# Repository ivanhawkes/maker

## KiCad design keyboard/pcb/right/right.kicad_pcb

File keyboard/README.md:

# Personal Split Keyboard

A personal keyboard project based on an accepted left-hand switch-position prototype. The goal is two mirrored, rechargeable keyboard halves communicating over Bluetooth Low Energy (BLE) with a separate desk controller connected to the PC by USB. The owner intends to print the cases on a Bambu Labs X2D.

**Status (2026-11-24):** design in progress. Both PCB halves are generated and fully routed by script, and pass KiCad's design rule check; their fabrication files are generated and checked on the computer ([PCB design](docs/pcb.md#fabrication-outputs-2026-11-24)); the firmware for both halves and the dongle compiles ([firmware](firmware/README.md)). Each half has a schematic drawn from its board, with KiCad's electrical rules check clean. Nothing has been fabricated or flashed, and there is no final case yet. Nothing here is verified on hardware.

## Prototype

The original files are preserved together in [prototype/left-hand/](prototype/left-hand/):

- [test-pad.fcstd](prototype/left-hand/test-pad.fcstd): existing FreeCAD prototype and starting point for the left-hand design.
- [test-pad.step](prototype/left-hand/test-pad.step) and [test-pad.3mf](prototype/left-hand/test-pad.3mf): existing 3D files.
- [test-pad-baseplate.dxf](prototype/left-hand/test-pad-baseplate.dxf): existing baseplate drawing; the DXF declares millimetres.

The geometry, switch count, dimensions, and relationships between the source and exports still need to be verified in FreeCAD. The layout is accepted, but small changes may be needed later.

## Documentation

- [Concept](docs/concept.md): the agreed shape of the keyboard, covering layout, electronics, firmware, mechanics and scope.
- [Requirements](docs/requirements.md): agreed goals and acceptance criteria.
- [Architecture](docs/architecture.md): proposed mechanical, electrical, and firmware approach and research links.
- [Decisions](docs/decisions.md): open questions and their design implications.
- [Development plan](docs/development-plan.md): staged work and deliverables for the future agent.
- [PCB design](docs/pcb.md): decisions, electrical design, fab rules, parts list and results.
- [PCB routing](docs/pcb-routing.md): how the boards are routed by script, and what was learned.
- [Case design](docs/case.md): the printed case for keyboard 1, how it is generated and checked, and its limits.
- [Retro case](docs/case-retro.md): the 1970s case for keyboard 2, built round the first case's insides.
- [Dongle case](docs/dongle-case.md): the printed case for the hand-wired dongle, and its wiring.
- [Showcase scenes](docs/scenes.md): the Blender files and stills of both keyboards, and how they are made.
- [Target controller](docs/controller.md): the board bought, a nice!nano clone, and the tests it must pass.
- [Filament on hand](docs/filament-on-hand.md): the owner's spools, for choosing colours.
- [Parts](parts/README.md): local footprints, 3D models and datasheets for every part.
- [Verification plan](docs/verification.md): digital checks and physical tests to plan and record.
- [AGENTS.md](AGENTS.md): shared instructions for agents; [CLAUDE.md](CLAUDE.md) imports them for Claude Code.

## Generating Everything

Run these from `keyboard/` inside the devenv shell, in this order. Each step reads what the one
before it wrote, so after a change run that step and everything below it. Every generator
checks its own output and exits with 1 if a check fails. FreeCAD comes from the system, not
the devenv ([PCB design](docs/pcb.md#running-the-tools)).

**1. Layout** ([layout/README.md](layout/README.md))

```sh
python tools/layout.py build       # layout/generated/ from layout/layout.yaml
python tools/layout.py check       # 28 keys a half, no overlaps (cutouts, real keycap outlines), exact mirror, outputs fresh
```

**2. Boards and schematics** ([PCB design](docs/pcb.md)). These need KiCad's own Python:

```sh
K=$(nix-store -qR "$(dirname "$(dirname "$(readlink -f "$(which kicad-cli)")")")")
PY=$(echo "$K" | grep 'python3-3.14.*-env

Open this directory as the project and select the desired available model in your Claude-enabled client. In Claude Code, the root `CLAUDE.md` imports the shared instructions. Ask the agent to start with the prototype inspection and decision review in the development plan. The PCB commands are `python tools/pcb_generate.py` (boards and schematics) and `python tools/pcb_check.py` (see [PCB design](docs/pcb.md#running-the-tools)). Claude's instruction-file loading can be checked with `/context all` where supported.)/bin/python3
YAML=$(dirname "$(dirname "$(python3 -c 'import yaml; print(yaml.__file__)')")")
export PYTHONPATH=$(echo "$K" | grep 'kicad-base-10')/lib/python3.14/site-packages:$YAML

"$PY" tools/pcb_generate.py        # both boards, routed, and their schematics; about 15 s
"$PY" tools/pcb_check.py           # design rules, electrical rules, schematic parity; about 40 s
"$PY" tools/pcb_review.py          # the boards' nets against the firmware's matrix
"$PY" tools/fab_generate.py        # Gerbers, drill files, placement and parts list in pcb/fab/, checked; about 8 s

for s in left right; do            # 1:1 prints for checking parts against the board
  kicad-cli pcb export pdf --mode-single --black-and-white --ev \
    --layers F.Cu,F.SilkS,F.Fab,Edge.Cuts -o pcb/print/$s-front.pdf pcb/$s/$s.kicad_pcb
  kicad-cli pcb export pdf --mode-single --black-and-white --ev --mirror \
    --layers B.Cu,B.SilkS,B.Fab,Edge.Cuts -o pcb/print/$s-back.pdf pcb/$s/$s.kicad_pcb
done
```

**3. Firmware shield** ([firmware/README.md](firmware/README.md), which also has the build commands)

```sh
python tools/zmk_generate.py            # the ZMK shield from pcb/pins.yaml and the layout
python tools/zmk_generate.py --check    # the shield is up to date
```

**4. Cases** ([case](docs/case.md), [retro case](docs/case-retro.md), [dongle case](docs/dongle-case.md))

```sh
"$PY" tools/case_board.py                 # board outlines and part positions, for the cases
FreeCADCmd tools/case_generate.py         # keyboard 1: tray, plate, lid; about 3 minutes
FreeCADCmd tools/wedge_generate.py        # its tenting wedges; about 1 minute
FreeCADCmd tools/case_retro_generate.py   # keyboard 2, the retro case; about 4 minutes
FreeCADCmd tools/dongle_generate.py       # the dongle's case; a few seconds
```

**5. Showcase scenes** ([scenes](docs/scenes.md))

```sh
FreeCADCmd tools/scene_export.py                                 # meshes for Blender; about 1 minute
blender -b --python tools/scene_build.py                         # the two .blend files only
blender -b --python tools/scene_build.py -- --render             # and 20 stills at 1920 x 1080
blender -b --python tools/scene_build.py -- --render --size 2k   # 20 stills at 2560 x 1440
blender -b --python tools/scene_build.py -- --render --size 4k   # 20 stills at 3840 x 2160
```

Stills go to `cad/scenes/renders/1080p/`, `2k/` or `4k/`. Add `--only kb1` or `--only retro` for
one keyboard. Rendering is on both graphics cards: the 4k set took under 10 minutes here.
Without a usable graphics card it falls back to the CPU, about eight times slower.

## Starting With Claude

Open this directory as the project and select the desired available model in your Claude-enabled client. In Claude Code, the root `CLAUDE.md` imports the shared instructions. Ask the agent to start with the prototype inspection and decision review in the development plan. The PCB commands are `python tools/pcb_generate.py` (boards and schematics) and `python tools/pcb_check.py` (see [PCB design](docs/pcb.md#running-the-tools)). Claude's instruction-file loading can be checked with `/context all` where supported.

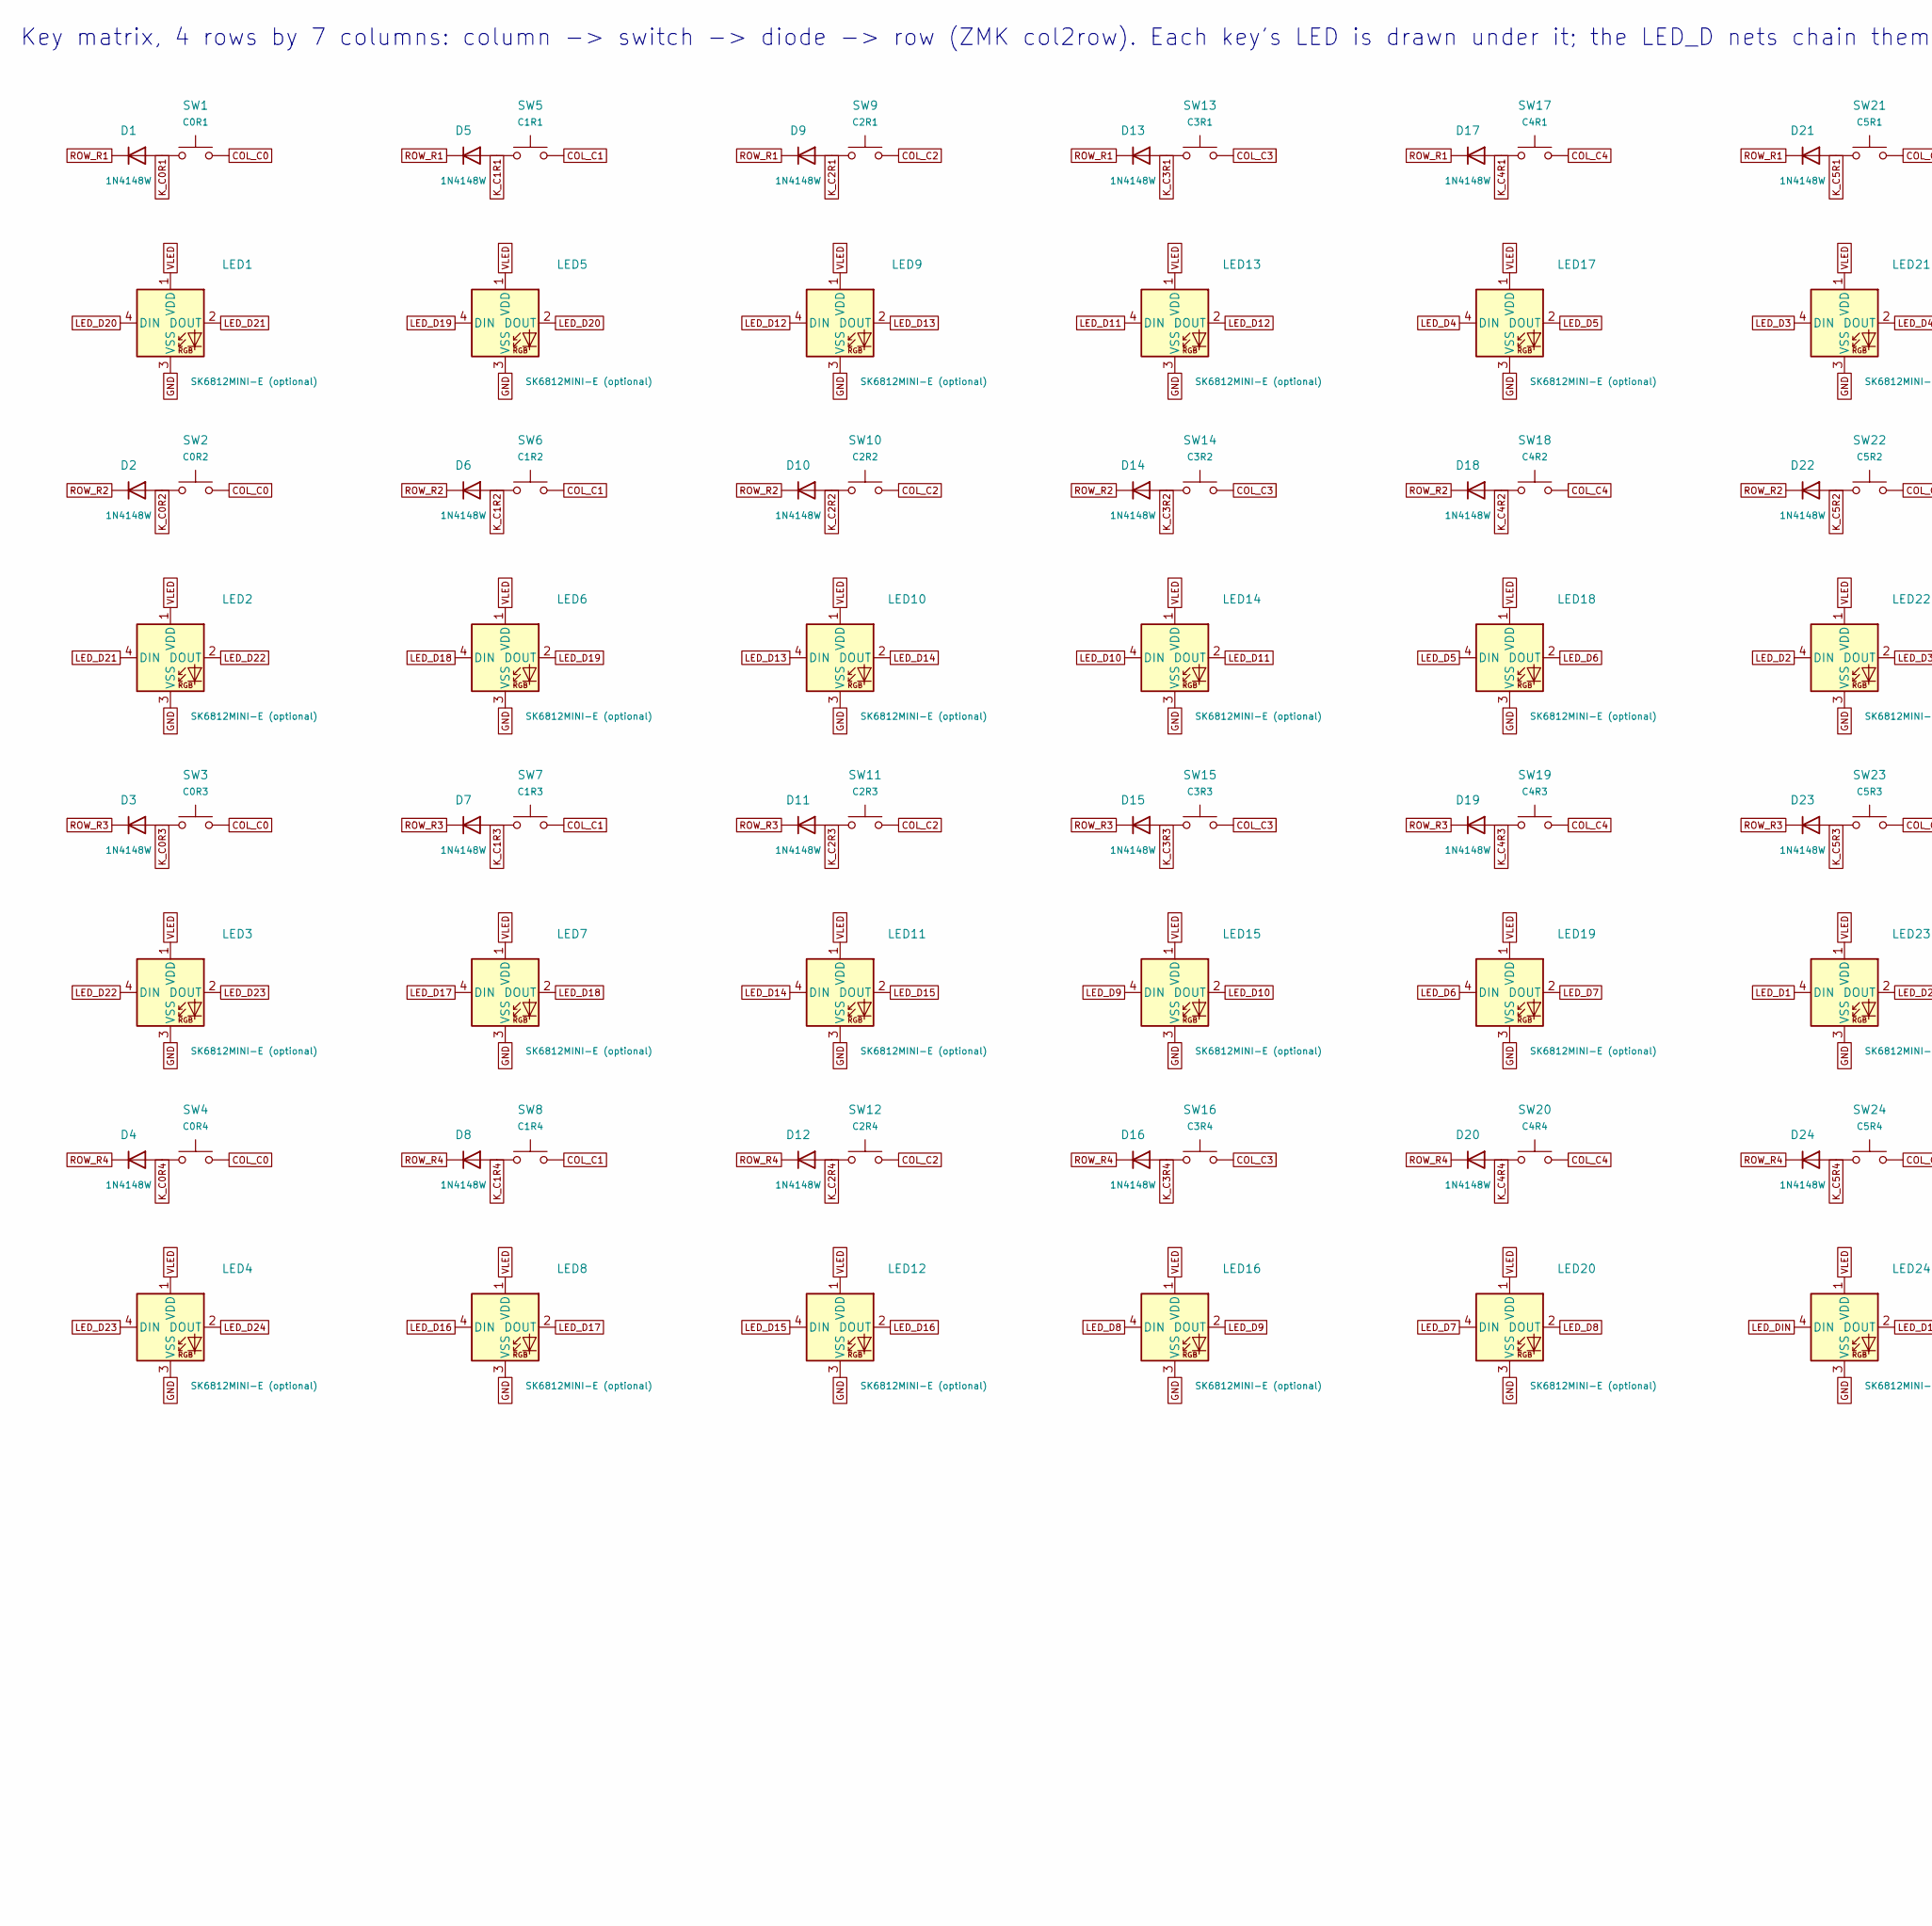
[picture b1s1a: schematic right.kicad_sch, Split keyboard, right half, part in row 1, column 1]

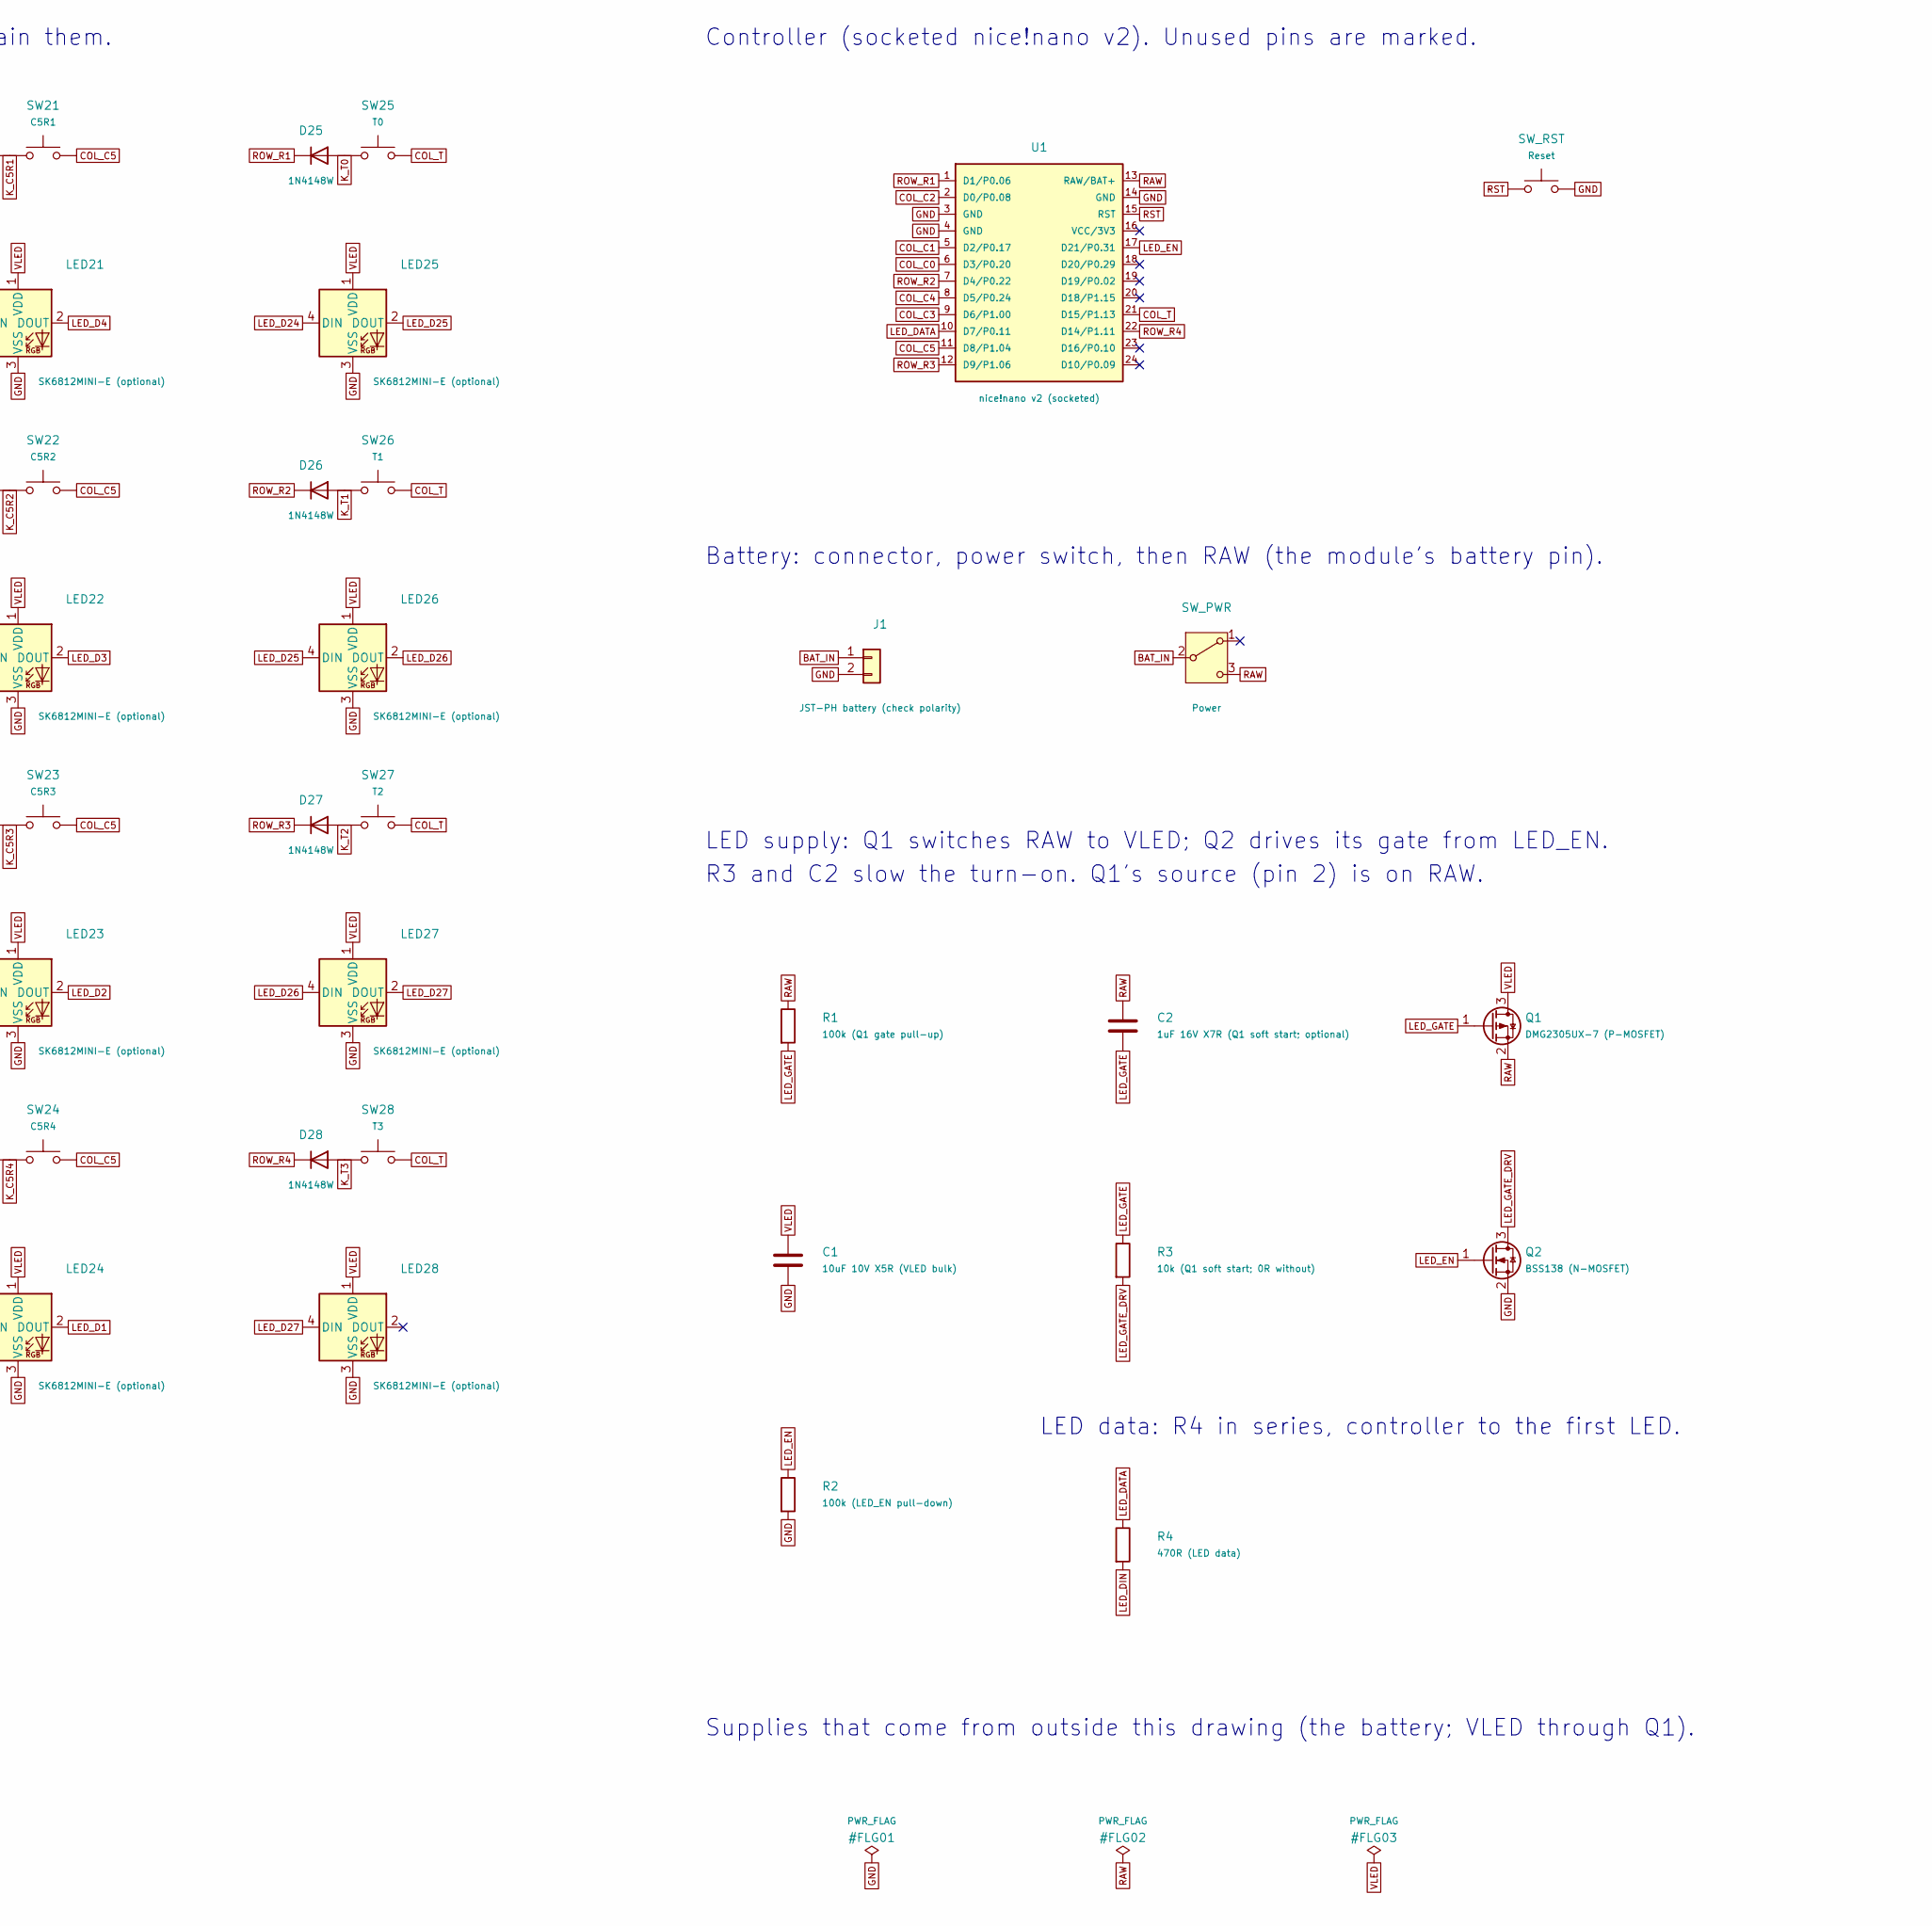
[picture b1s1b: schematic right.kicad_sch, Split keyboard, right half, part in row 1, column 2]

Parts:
C1: 10uF 10V X5R (VLED bulk); C_1206_3216Metric_Pad1.33x1.80mm_HandSolder
C2: 1uF 16V X7R (Q1 soft start; optional); C_1206_3216Metric_Pad1.33x1.80mm_HandSolder
D1, D2, D3, D4, D5, D6, D7, D8, D9, D10, D11, D12, D13, D14, D15, D16, D17, D18, D19, D20, D21, D22, D23, D24, D25, D26, D27, D28: 1N4148W; D_SOD-123
J1: JST-PH battery (check polarity); JST_PH_S2B-PH-K_1x02_P2.00mm_Horizontal
LED1, LED2, LED3, LED4, LED5, LED6, LED7, LED8, LED9, LED10, LED11, LED12, LED13, LED14, LED15, LED16, LED17, LED18, LED19, LED20, LED21, LED22, LED23, LED24, LED25, LED26, LED27, LED28: SK6812MINI-E (optional); LED_SK6812MINI-E_3.2x2.8mm_P1.5mm_ReverseMount
Q1: DMG2305UX-7 (P-MOSFET); SOT-23_Handsoldering
Q2: BSS138 (N-MOSFET); SOT-23_Handsoldering
R1: 100k (Q1 gate pull-up); R_1206_3216Metric_Pad1.30x1.75mm_HandSolder
R2: 100k (LED_EN pull-down); R_1206_3216Metric_Pad1.30x1.75mm_HandSolder
R3: 10k (Q1 soft start; 0R without); R_1206_3216Metric_Pad1.30x1.75mm_HandSolder
R4: 470R (LED data); R_1206_3216Metric_Pad1.30x1.75mm_HandSolder
SW1: C0R1; SW_MX_HS_CPG151101S11_1u
SW2: C0R2; SW_MX_HS_CPG151101S11_1u
SW3: C0R3; SW_MX_HS_CPG151101S11_1u
SW4: C0R4; SW_MX_HS_CPG151101S11_1u
SW5: C1R1; SW_MX_HS_CPG151101S11_1u
SW6: C1R2; SW_MX_HS_CPG151101S11_1u
SW7: C1R3; SW_MX_HS_CPG151101S11_1u
SW8: C1R4; SW_MX_HS_CPG151101S11_1u
SW9: C2R1; SW_MX_HS_CPG151101S11_1u
SW10: C2R2; SW_MX_HS_CPG151101S11_1u
SW11: C2R3; SW_MX_HS_CPG151101S11_1u
SW12: C2R4; SW_MX_HS_CPG151101S11_1u
SW13: C3R1; SW_MX_HS_CPG151101S11_1u
SW14: C3R2; SW_MX_HS_CPG151101S11_1u
SW15: C3R3; SW_MX_HS_CPG151101S11_1u
SW16: C3R4; SW_MX_HS_CPG151101S11_1u
SW17: C4R1; SW_MX_HS_CPG151101S11_1u
SW18: C4R2; SW_MX_HS_CPG151101S11_1u
SW19: C4R3; SW_MX_HS_CPG151101S11_1u
SW20: C4R4; SW_MX_HS_CPG151101S11_1u
SW21: C5R1; SW_MX_HS_CPG151101S11_1u
SW22: C5R2; SW_MX_HS_CPG151101S11_1u
SW23: C5R3; SW_MX_HS_CPG151101S11_1u
SW24: C5R4; SW_MX_HS_CPG151101S11_1u
SW25: T0; SW_MX_HS_CPG151101S11_1u
SW26: T1; SW_MX_HS_CPG151101S11_1u
SW27: T2; SW_MX_HS_CPG151101S11_1u
SW28: T3; SW_MX_HS_CPG151101S11_1u
SW_PWR: Power; SW_SPDT_PCM12
SW_RST: Reset; SW_SPST_TL3342
U1: nice!nano v2 (socketed); ProMicro_Reversible_Single

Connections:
BAT_IN: J1.1, SW_PWR.2 (B)
COL_C0: SW1.2, SW2.2, SW3.2, SW4.2, U1.6 (D3/P0.20)
COL_C1: SW5.2, SW6.2, SW7.2, SW8.2, U1.5 (D2/P0.17)
COL_C2: SW9.2, SW10.2, SW11.2, SW12.2, U1.2 (D0/P0.08)
COL_C3: SW13.2, SW14.2, SW15.2, SW16.2, U1.9 (D6/P1.00)
COL_C4: SW17.2, SW18.2, SW19.2, SW20.2, U1.8 (D5/P0.24)
COL_C5: SW21.2, SW22.2, SW23.2, SW24.2, U1.11 (D8/P1.04)
COL_T: SW25.2, SW26.2, SW27.2, SW28.2, U1.21 (D15/P1.13)
GND: C1.2, J1.2, LED1.3 (VSS), LED2.3 (VSS), LED3.3 (VSS), LED4.3 (VSS), LED5.3 (VSS), LED6.3 (VSS), LED7.3 (VSS), LED8.3 (VSS), LED9.3 (VSS), LED10.3 (VSS), LED11.3 (VSS), LED12.3 (VSS), LED13.3 (VSS), LED14.3 (VSS), LED15.3 (VSS), LED16.3 (VSS), LED17.3 (VSS), LED18.3 (VSS), LED19.3 (VSS), LED20.3 (VSS), LED21.3 (VSS), LED22.3 (VSS), LED23.3 (VSS), LED24.3 (VSS), LED25.3 (VSS), LED26.3 (VSS), LED27.3 (VSS), LED28.3 (VSS), Q2.2 (S), R2.2, SW_RST.2, U1.3 (GND), U1.4 (GND), U1.14 (GND)
K_C0R1: D1.2 (A), SW1.1
K_C0R2: D2.2 (A), SW2.1
K_C0R3: D3.2 (A), SW3.1
K_C0R4: D4.2 (A), SW4.1
K_C1R1: D5.2 (A), SW5.1
K_C1R2: D6.2 (A), SW6.1
K_C1R3: D7.2 (A), SW7.1
K_C1R4: D8.2 (A), SW8.1
K_C2R1: D9.2 (A), SW9.1
K_C2R2: D10.2 (A), SW10.1
K_C2R3: D11.2 (A), SW11.1
K_C2R4: D12.2 (A), SW12.1
K_C3R1: D13.2 (A), SW13.1
K_C3R2: D14.2 (A), SW14.1
K_C3R3: D15.2 (A), SW15.1
K_C3R4: D16.2 (A), SW16.1
K_C4R1: D17.2 (A), SW17.1
K_C4R2: D18.2 (A), SW18.1
K_C4R3: D19.2 (A), SW19.1
K_C4R4: D20.2 (A), SW20.1
K_C5R1: D21.2 (A), SW21.1
K_C5R2: D22.2 (A), SW22.1
K_C5R3: D23.2 (A), SW23.1
K_C5R4: D24.2 (A), SW24.1
K_T0: D25.2 (A), SW25.1
K_T1: D26.2 (A), SW26.1
K_T2: D27.2 (A), SW27.1
K_T3: D28.2 (A), SW28.1
LED_D1: LED23.4 (DIN), LED24.2 (DOUT)
LED_D2: LED22.4 (DIN), LED23.2 (DOUT)
LED_D3: LED21.4 (DIN), LED22.2 (DOUT)
LED_D4: LED17.4 (DIN), LED21.2 (DOUT)
LED_D5: LED17.2 (DOUT), LED18.4 (DIN)
LED_D6: LED18.2 (DOUT), LED19.4 (DIN)
LED_D7: LED19.2 (DOUT), LED20.4 (DIN)
LED_D8: LED16.4 (DIN), LED20.2 (DOUT)
LED_D9: LED15.4 (DIN), LED16.2 (DOUT)
LED_D10: LED14.4 (DIN), LED15.2 (DOUT)
LED_D11: LED13.4 (DIN), LED14.2 (DOUT)
LED_D12: LED9.4 (DIN), LED13.2 (DOUT)
LED_D13: LED9.2 (DOUT), LED10.4 (DIN)
LED_D14: LED10.2 (DOUT), LED11.4 (DIN)
LED_D15: LED11.2 (DOUT), LED12.4 (DIN)
LED_D16: LED8.4 (DIN), LED12.2 (DOUT)
LED_D17: LED7.4 (DIN), LED8.2 (DOUT)
LED_D18: LED6.4 (DIN), LED7.2 (DOUT)
LED_D19: LED5.4 (DIN), LED6.2 (DOUT)
LED_D20: LED1.4 (DIN), LED5.2 (DOUT)
LED_D21: LED1.2 (DOUT), LED2.4 (DIN)
LED_D22: LED2.2 (DOUT), LED3.4 (DIN)
LED_D23: LED3.2 (DOUT), LED4.4 (DIN)
LED_D24: LED4.2 (DOUT), LED25.4 (DIN)
LED_D25: LED25.2 (DOUT), LED26.4 (DIN)
LED_D26: LED26.2 (DOUT), LED27.4 (DIN)
LED_D27: LED27.2 (DOUT), LED28.4 (DIN)
LED_DATA: R4.1, U1.10 (D7/P0.11)
LED_DIN: LED24.4 (DIN), R4.2
LED_EN: Q2.1 (G), R2.1, U1.17 (D21/P0.31)
LED_GATE: C2.2, Q1.1 (G), R1.2, R3.1
LED_GATE_DRV: Q2.3 (D), R3.2
RAW: C2.1, Q1.2 (S), R1.1, SW_PWR.3 (C), U1.13 (RAW/BAT+)
ROW_R1: D1.1 (K), D5.1 (K), D9.1 (K), D13.1 (K), D17.1 (K), D21.1 (K), D25.1 (K), U1.1 (D1/P0.06)
ROW_R2: D2.1 (K), D6.1 (K), D10.1 (K), D14.1 (K), D18.1 (K), D22.1 (K), D26.1 (K), U1.7 (D4/P0.22)
ROW_R3: D3.1 (K), D7.1 (K), D11.1 (K), D15.1 (K), D19.1 (K), D23.1 (K), D27.1 (K), U1.12 (D9/P1.06)
ROW_R4: D4.1 (K), D8.1 (K), D12.1 (K), D16.1 (K), D20.1 (K), D24.1 (K), D28.1 (K), U1.22 (D14/P1.11)
RST: SW_RST.1, U1.15 (RST)
VLED: C1.1, LED1.1 (VDD), LED2.1 (VDD), LED3.1 (VDD), LED4.1 (VDD), LED5.1 (VDD), LED6.1 (VDD), LED7.1 (VDD), LED8.1 (VDD), LED9.1 (VDD), LED10.1 (VDD), LED11.1 (VDD), LED12.1 (VDD), LED13.1 (VDD), LED14.1 (VDD), LED15.1 (VDD), LED16.1 (VDD), LED17.1 (VDD), LED18.1 (VDD), LED19.1 (VDD), LED20.1 (VDD), LED21.1 (VDD), LED22.1 (VDD), LED23.1 (VDD), LED24.1 (VDD), LED25.1 (VDD), LED26.1 (VDD), LED27.1 (VDD), LED28.1 (VDD), Q1.3 (D)

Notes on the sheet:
Key matrix, 4 rows by 7 columns: column -> switch -> diode -> row (ZMK col2row). Each key's LED is drawn under it; the LED_D nets chain them.
Controller (socketed nice!nano v2). Unused pins are marked.
Battery: connector, power switch, then RAW (the module's battery pin).
LED supply: Q1 switches RAW to VLED; Q2 drives its gate from LED_EN.
R3 and C2 slow the turn-on. Q1's source (pin 2) is on RAW.
LED data: R4 in series, controller to the first LED.
Supplies that come from outside this drawing (the battery; VLED through Q1).

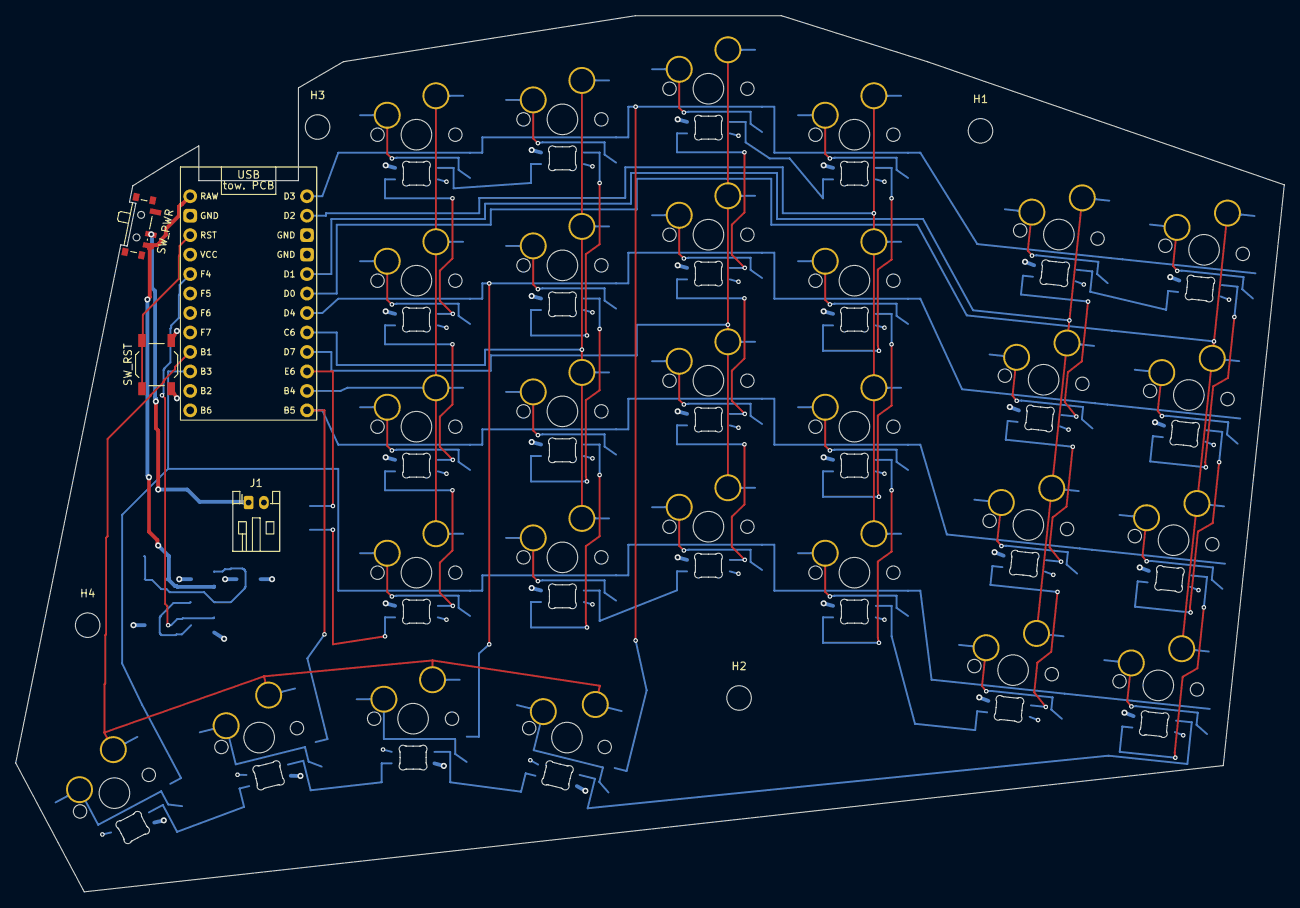
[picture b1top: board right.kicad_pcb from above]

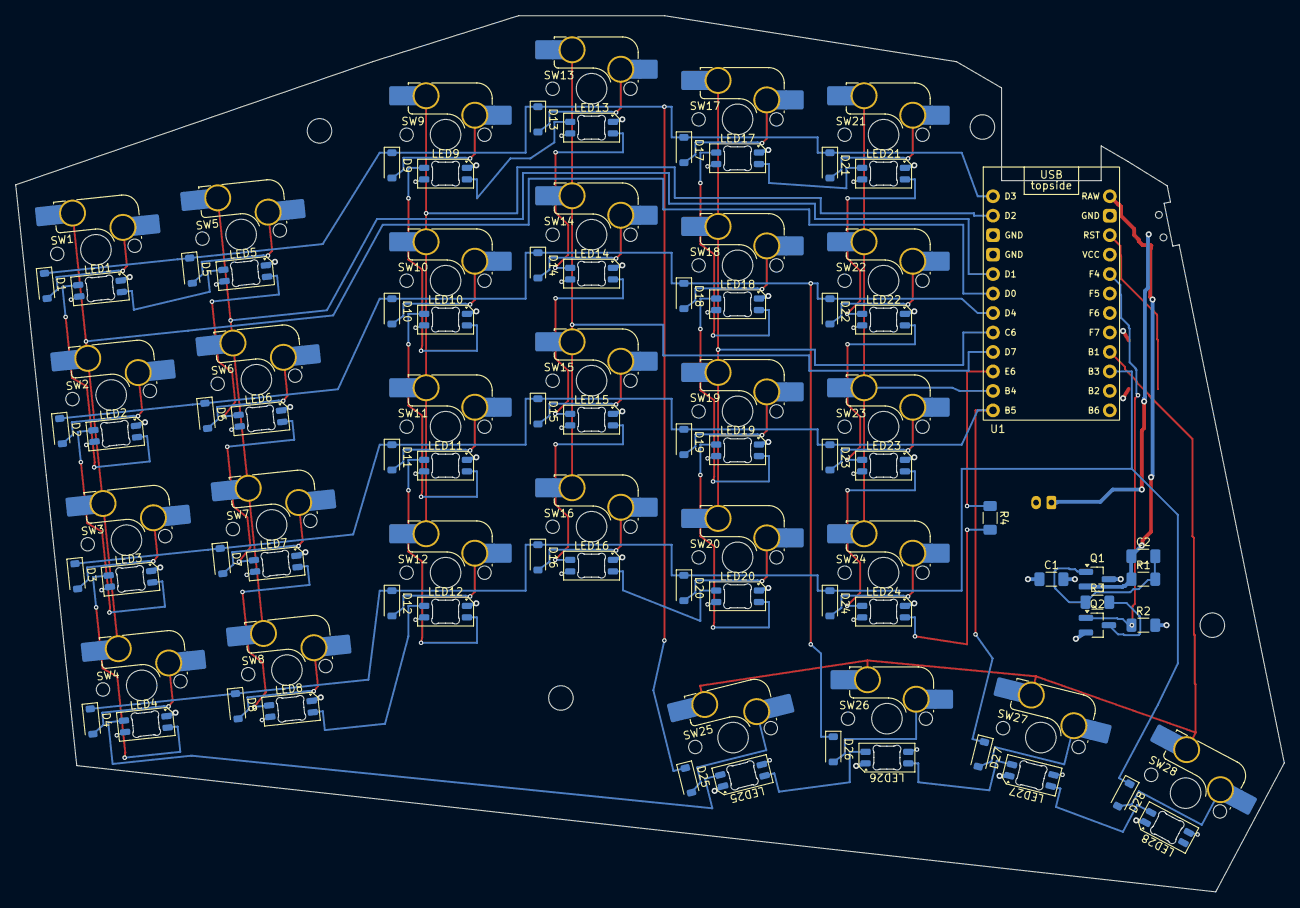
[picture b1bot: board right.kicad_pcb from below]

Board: 4 copper layers, 165.5 x 114.3 mm, 100 parts (93 on the bottom side), 76 nets.

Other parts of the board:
H1, H2, H3, H4: M3 mounting hole; MountingHole_3.2mm_M3

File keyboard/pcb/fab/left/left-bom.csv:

Refs,Value,Footprint,Qty
C1,10uF 10V X5R (VLED bulk),C_1206_3216Metric_Pad1.33x1.80mm_HandSolder,1
C2,1uF 16V X7R (Q1 soft start; optional),C_1206_3216Metric_Pad1.33x1.80mm_HandSolder,1
D1 D2 D3 D4 D5 D6 D7 D8 D9 D10 D11 D12 D13 D14 D15 D16 D17 D18 D19 D20 D21 D22 D23 D24 D25 D26 D27 D28,1N4148W,D_SOD-123,28
J1,JST-PH battery (check polarity),JST_PH_S2B-PH-K_1x02_P2.00mm_Horizontal,1
LED1 LED2 LED3 LED4 LED5 LED6 LED7 LED8 LED9 LED10 LED11 LED12 LED13 LED14 LED15 LED16 LED17 LED18 LED19 LED20 LED21 LED22 LED23 LED24 LED25 LED26 LED27 LED28,SK6812MINI-E (optional),LED_SK6812MINI-E_3.2x2.8mm_P1.5mm_ReverseMount,28
Q1,DMG2305UX-7 (P-MOSFET),SOT-23_Handsoldering,1
Q2,BSS138 (N-MOSFET),SOT-23_Handsoldering,1
R1,100k (Q1 gate pull-up),R_1206_3216Metric_Pad1.30x1.75mm_HandSolder,1
R2,100k (LED_EN pull-down),R_1206_3216Metric_Pad1.30x1.75mm_HandSolder,1
R3,10k (Q1 soft start; 0R without),R_1206_3216Metric_Pad1.30x1.75mm_HandSolder,1
R4,470R (LED data),R_1206_3216Metric_Pad1.30x1.75mm_HandSolder,1
SW1 SW2 SW3 SW4 SW5 SW6 SW7 SW8 SW9 SW10 SW11 SW12 SW13 SW14 SW15 SW16 SW17 SW18 SW19 SW20 SW21 SW22 SW23 SW24 SW25 SW26 SW27 SW28,Key switch socket,SW_MX_HS_CPG151101S11_1u,28
SW_PWR,Power,SW_SPDT_PCM12,1
SW_RST,Reset,SW_SPST_TL3342,1

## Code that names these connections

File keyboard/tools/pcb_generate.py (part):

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run. Run kicad-cli DRC afterwards.

LED supply (option B, owner 2026-11-23): VLED is RAW (the battery, 3.0-4.2 V) through a
high-side P-MOSFET, Q1, driven by a small N-MOSFET, Q2, from the LED_EN pin (pins.yaml).
R2 holds LED_EN low, so the LEDs are off unless the firmware turns them on. Each LED draws
about 1 mA even when dark (datasheet), hence the hardware switch. R3 and C2 slow Q1's turn-on
(inrush into C1); R4 is in series with the LED data, which the LED datasheet asks for and which
limits the current into the first LED when the pin is high with VLED off (review, 2026-11-23).

Battery path: JST-PH -> power switch -> nice!nano RAW pin. The official nice!nano v2
pinout labels RAW "BATTERY+" (as well as the extra B+ pad, which is not socketed).
Copper keep-outs cover the area between the controller's pin rows and a strip beyond its
antenna end (see CONTROLLER_KEEPOUTS); the antenna position on the module is unverified.
Four layers: signals on F.Cu and B.Cu, a GND plane on In1.Cu and a VLED plane on In2.Cu.
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        pad_net[pad] = f"ROW_{row}"
    for col, pad in pins["columns"].items():
        pad_net[pad] = f"COL_{col}"
    pad_net[pins["led_data"]] = "LED_DATA"  # through R4 to LED_DIN, the first LED's input
    for pad in pins["power"]["gnd"]:
        pad_net[pad] = "GND"
    pad_net[pins["power"]["rst"]] = "RST"
    # The module's 3.3 V output (pins.yaml power.vcc) is not used: its pad has no net, like the
    # spare GPIO pads, and the schematic marks them all as unconnected.
    pad_net[pins["power"]["raw"]] = "RAW"
    pad_net[pins["led_power_enable"]] = "LED_EN"

    # Switches, diodes and LEDs.
    led_order = []
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    if side == "right":
        # Decided (owner, 2026-11-23): on the right half the nice!nano mounts upside down
        # (components towards the PCB), the usual practice on split boards, which mirrors its
        # pins: the matrix pins (pads 1-12) then face the keys and RAW/RST face the power switch
        # and reset, as on the left. In KiCad that is the footprint flipped in x.
        u.Flip(u.GetPosition(), pcbnew.FLIP_DIRECTION_LEFT_RIGHT)  # checked: pad 1 at (-44.38, 33.97)
    for pad_no, net in pad_net.items():
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    # upright) is in series: the F.Cu run drops through a via to R4's upper pad and resumes
    # from a via at its lower pad.
    first = chain[0]
    din, dpad = pad_of(first[3], "4"), upads[str(pins["led_data"])]
    r4 = B.place(load(STOCK / "Resistor_SMD.pretty", "R_1206_3216Metric_Pad1.30x1.75mm_HandSolder"), "R4",
                 LED_DATA_R_AT[0] * sx, LED_DATA_R_AT[1], 90.0, True, "470R (LED data)")
    r4_up, r4_down = sorted(r4.Pads(), key=lambda p: p.GetPosition().y)  # board y grows towards the user
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    trunk = (pcbnew.ToMM(trunk_end.x), pcbnew.ToMM(trunk_end.y), (0,))
    # Longest first: the router has no rip-up, so a later net must find its way round earlier ones.
    jobs = (
        ("COL_T", [term(upads[str(pins["columns"]["T"])]), trunk]),
        ("RST", [term(upads[str(pins["power"]["rst"])])] + terms(rst, "1")),
        ("LED_EN", [term(upads[str(pins["led_power_enable"])])] + terms(lsw["Q2"], "1") + terms(lsw["R2"], "1")),
        ("BAT_IN", terms(j, "1") + terms(s, "2")),
        ("RAW", [term(upads[str(pins["power"]["raw"])])] + terms(s, on_pad) + terms(lsw["Q1"], "2") + terms(lsw["R1"], "1")
         + terms(lsw["C2"], "1")),
        ("LED_GATE", terms(lsw["Q1"], "1") + terms(lsw["R3"], r3_gate.GetNumber()) + terms(lsw["R1"], "2") + terms(lsw["C2"], "2")),
        ("LED_GATE_DRV", terms(lsw["Q2"], "3") + terms(lsw["R3"], r3_drv.GetNumber())),
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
